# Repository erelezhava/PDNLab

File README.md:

# PDNLab DC

Open-source DC power-integrity (IR drop) solver for PCBs. Own solver code, KiCad 10 boards as the first input, Apache-2.0.

**Status: Phase 2 (real boards), no release yet.** A KiCad 10 board runs end to
end: `init`, `check` and `run` (below) give a settled DC drop with maps and tables.

Current support and limits:

- Input: KiCad 10 boards, through KiCad's IPC-2581 export (`kicad-cli`, run for
  you by `init`, `check` and `run`). Other EDA tools are not supported.
- One rail per setup file: one `[[source]]` and its `[[load]]`s. Several rails
  sharing GND are refused for now: GND solved per rail would leave out the other
  rails' return current (planned; see the [roadmap](docs/roadmap.md), increment G).
- A board run needs the external Gmsh executable on `PATH` (see Setup).
- Not checked yet: copper outside the board outline (KiCad's DRC catches it; the
  importer does not read the outline), and copper of two nets that only touch
  along an edge (an overlap is caught). Run KiCad's DRC first.
- Results are for review, not sign-off: release 0.1 waits for its gates (see
  the [roadmap](docs/roadmap.md)).

Measured results and limitations are in [the result log](docs/DECISIONS.md); the
current licences and packaging boundaries in the
[dependency inventory](docs/dependency-license-audit.md).

See the [development plan](docs/project-plan.md) for scope, architecture,
experiments and release gates.

## Setup

```sh
uv sync          # creates .venv with numpy, scipy, meshio and pytest
uv run pytest    # runs the analytic tests
```

Without uv: `pip install -e . pytest`, then `pytest`.

Experiments 2 to 4 also need the external Gmsh executable on `PATH`. On Ubuntu:

```sh
sudo apt install gmsh
gmsh --version
```

Without Gmsh, the integration tests that need it are skipped. CI installs it so
those tests run there too. The solver never imports the Gmsh Python API.

## Describing a simulation

A simulation is described by a TOML setup file, by pins. Start from the KiCad
board: `init` exports it with KiCad's own `kicad-cli` (on `PATH`, or named by
`PDNLAB_KICAD_CLI`) into a `pdnlab/` folder in the project and writes a form to
fill in there. An IPC-2581 export (`.xml`) works too.

```sh
uv run pdnlab-dc init path/to/project/board.kicad_pcb
# writes path/to/project/pdnlab/board.xml and path/to/project/pdnlab/setup.toml
# fill in plating_um, the [[source]] and the [[load]]s; pin names are listed at
# the bottom of the file, net by net
uv run pdnlab-dc check path/to/project/pdnlab/setup.toml   # says what will be simulated
```

A `[[source]]` holds its `power_pins` at `volts`, a `[[load]]` draws `amps`; each
lists its `power_pins` and `gnd_pins`, and the pins of one list are joined (one
group). `U1.*` means every pin of U1 on that list's net, so hidden power and GND
pins are not missed; `check` says how many pins each wildcard added. When the
`.kicad_pcb` is newer than its export, `check` and `run` export it again.

## Running a simulation

```sh
uv run pdnlab-dc run path/to/project/pdnlab/setup.toml
```

The rail's power net and the GND net are solved as separate networks carrying
the same currents; each load sees V(power) − V(GND). One rail per setup file for
now (see the limits above). The mesh is made finer
(scale 1, 0.5, 0.25, 0.125) until the voltage every load sees changes by at most
the tolerance (default 10 µV + 1 % of its drop; `[options] tolerance_uv` and
`tolerance_percent`).

Results go to `results/<setup name>/` next to the setup file (in a KiCad
project: `pdnlab/results/setup/`); earlier results are replaced only with
`--force`:

- `summary.txt`: per load the voltage it sees and its drop, split into power and
  GND; the refinement check round by round, with memory per round; per net
  losses, the solver's checks, current-density hot spots per layer (peak, and
  averaged over a 0.25 mm disk) and the highest barrel currents; the
  assumptions.
- `loads.csv`, `pins.csv` (each pin's share of its group's current), `vias.csv`
  (each plated hole's largest barrel current).
- Per net and layer: `<net>_<layer>.vtu` for ParaView (voltage, drop in mV,
  current density in A/mm²) and `<net>_<layer>_voltage.png` /
  `<net>_<layer>_current.png`.

Memory: a refinement round is not started if its predicted memory (from the last
round's measured peak, with a 1.5× margin) exceeds `[options] max_memory_gb`
(default: half of the computer's RAM) or the free memory. The last completed
round is then reported, marked NOT SETTLED, and `run` exits with code 2. A hard
ceiling (the limit + 2 GB, inherited by Gmsh) turns a wrong estimate into an
out-of-memory message instead of a frozen machine. Exit codes: 0 settled, 1 not
solved (the message says what to fix), 2 not settled.

## Prepared solver (phase 1)

Existing assembly, ties and resistor primitives remain in `pdnlab_dc.fem`;
barrel resistance is in `pdnlab_dc.vias`. Prepare the final electrical matrix
after tying nodes and stamping resistors:

```python
from pdnlab_dc.solver import prepare_fixed_voltages

system = prepare_fixed_voltages(matrix, fixed_nodes)
v = system.solve(3.3, injected_current)  # positive into copper; sinks negative
v_next = system.solve(3.3, next_current)  # reuses the same factorization
# Optional: observed voltage per +1 A, with fixed voltages at zero:
z = system.transfer_resistance(load_nodes, batch_size=8)
print(system.stats, system.last_solve)
```

Preparation copies the matrix and fixed indices. Reprepare if conductances or
fixed-node membership change; current and fixed-voltage values may change
without preparation. The one-shot `fem.solve_fixed_voltages` remains compatible
and delegates to this solver. Every component still needs a fixed node.
Sources here are voltages to a reference, not arbitrary two-terminal sources.
The input is a conservative nodal matrix, with ground represented explicitly;
material nonzero row sums (including implicit ground shunts) are rejected.
Each connected network is solved relative to one of its fixed voltages, then
shifted back, reducing sensitivity to the rail's absolute voltage.

Transfer extraction bounds full-field RHS/solution columns by `batch_size`,
but its returned dense observation-by-injection matrix can still be large.
It is never built by `solve`. A selected electrical node may represent a tied
finite contact; selecting a bare mesh vertex does not validate point-contact
physics. Explicit area contacts are available through the network interface below.

`system.stats` reports preparation/factorization time, nonzero counts and
sparse-array bytes; it does not measure peak RSS or native LU workspace.
`system.last_solve` records elapsed time and RHS batching. Independent loss
integration and conservation checks remain in `pdnlab_dc.checks` and require
original sheet geometry and branch data from the caller.
Checks normalize reactions and terminal power to the same per-network origin.
They require both global and per-network current balance; independent loss
integration and per-via checks retain their existing tolerances.

Run the synthetic performance probe (no private boards):

```sh
uv run python experiments/phase1_solver_benchmark.py
```

The primary probe solves relative to zero. A separate 3.3 V probe now gates
reference invariance and conservation. The formerly failing power-check case
and its correction are recorded in the result log. Very large common-mode
voltages relative to the drop remain limited by floating-point resolution.
The real-board experiment's transfer/scenario workflow has not been migrated.

## Named synthetic networks

`pdnlab_dc.network.Network` composes the validated primitives without manual
sparse-matrix wiring. All geometry/material inputs use SI units:

```python
from pdnlab_dc.network import Network
from pdnlab_dc.simple_meshes import rectangle_mesh

nodes, triangles, left, right = rectangle_mesh(0.05, 0.005, 12, 4)
net = Network()
net.add_sheet("top", nodes, triangles, sheet_conductance=35e-6 / 1.724e-8)
net.add_terminal("source", "top", left)
net.add_terminal("load", "top", right)
prepared = net.prepare(["source"])
result = prepared.solve({"source": 3.3}, {"load": 0.1})
assert result.passed, result.checks
next_case = prepared.solve({"source": 3.3}, {"load": 0.2})  # same LU
```

Terminal selections are disjoint node groups on one sheet. By default their
nodes are tied equipotential, representing an ideal soldered pad/rim. Passing
explicit `weights=[...]` leaves them untied and allocates sink current by those
nonnegative fractions, in selected-node order. There is no implicit equal
allocation for an untied group. Use `add_contact` below for explicit finite-area
polygons; a bare vertex still has point-contact mesh dependence.

Use `add_resistor(name, a, b, resistance)` between equipotential terminals.
Use `add_barrel(name, a, b, length=..., inner_radius=..., outer_radius=...,
resistivity=...)` between terminals declared with `rim=True` on distinct
sheets. Rims stay separate electrical unknowns; each declared rim must have
an incident branch. The caller supplies contacted layers and copper radii.

Preparation snapshots the builder. Source membership then stays fixed;
`solve` requires exactly those source-voltage names and accepts nonnegative
sink currents by load-terminal name. Unspecified loads draw zero. Unknown
loads, loads at fixed sources, overlapping selections and floating components
raise errors instead of silently changing a case. Source terminal currents
may be positive (supplying) or negative (absorbing).

Results include electrical and per-sheet voltages, per-selected-node terminal
voltages, external terminal currents (positive into copper), branch currents
(declared a → b), independently integrated sheet/branch losses, timings and
conservation checks. Rim KCL includes sheet, every incident branch and any
external current at that rim. Check `result.passed`: failed checks are returned
with their residuals and tolerances. `prepared.node_map` gives copies mapping
original sheet nodes to electrical unknowns.

`prepared.stats` separates sheet assembly, area-contact selection, composition
and solver preparation;
`prepared.last_solve` exposes the last low-level solve/transfer timing and RHS
statistics. Its solver sparse-byte count excludes the wrapper's check matrix,
original sheet matrices, geometry and mappings; it is not whole-model memory.
`prepared.transfer_resistance(["load"], batch_size=8)` optionally extracts Z
in requested name order for equipotential terminals only.

Run the three-layer analytic example with named pads/rims and two barrel
segments, at two mesh resolutions and two current levels:

```sh
uv run python experiments/phase1_network_cases.py
```

## Finite-area contacts

`Network.add_contact(name, sheet, region, model=...)` selects an explicit
Shapely `Polygon` in mesh coordinates (metres), including its position and area:

```python
from shapely.geometry import box

# For the strip above: feed ends on the first grid line; touch may cut cells.
contact_net = Network()
contact_net.add_sheet("top", nodes, triangles, 35e-6 / 1.724e-8)
contact_net.add_contact("feed", "top", box(0, 0, 0.05 / 12, 0.005))
contact_net.add_contact("touch", "top", box(0.025, 0, 0.035, 0.005),
                        model="uniform_current")
contact_model = contact_net.prepare(["feed"])
case = contact_model.solve({"feed": 3.3}, {"touch": 0.1})
assert case.passed, case.checks
print(case.contact_voltages_v["touch"])  # area-average copper voltage
```

- `equipotential` (default) is an ideal electrode shorting only its specified
  area. Its boundary must conform to the existing mesh: materially cut
  triangles raise instead of silently changing the electrode's size. It can
  be a fixed-voltage source or a current sink; the solve determines sharing.
- `uniform_current` prescribes constant current per area without tying the
  copper. Triangle intersections are integrated to obtain FEM nodal load
  weights and the area-average voltage. It supports current sinks, including
  patches whose edges cut triangles. Its support vertices may lie outside the
  polygon; the integrated patch itself is not enlarged. It is not a fixed-
  voltage source or an equipotential terminal for transfer extraction.

These are distinct idealizations of contact behaviour. No contact resistivity,
pressure-dependent distribution or 3D interface model is inferred. The region
must be a valid positive-area 2D polygon fully covered by nonoverlapping copper
elements. Clipping outside copper, nearest-node fallback and zero-area point
regions are rejected. Shared terminal support is still unsupported: refine if
two disjoint physical contacts share coarse-mesh vertices. Automatic remeshing
and pad/importer integration remain later work.

`prepared.contact_info` reports model, bounds, requested/covered area and support
size. `result.contact_voltages_v` reports the electrode voltage or uniform-area
mean; `terminal_voltages_v` still returns all selected nodal voltages. The
standalone `pdnlab_dc.contacts.select_area_contact` exposes the selection and
weights for other callers. Geometry checks use a 1e-10 relative area tolerance;
electrical conservation and analytic tolerances are unchanged.

Run finite-electrode and uniform-patch convergence against analytic references,
with a separate mathematical-point diagnostic:

```sh
uv run python experiments/phase1_contact_cases.py
```

The diagnostic point's voltage grows with refinement; it is not reported as a
physical contact-resistance prediction. The finite circular electrode uses a
fixed 128-sided polygon, so its circle-reference error includes polygon geometry.

## Phase 2 board-model scaffold

`pdnlab_dc.board` contains immutable neutral records for source provenance,
layers, nets, copper features, physical pin pads and drill features. `BoardModel`
validates IDs, references, SI dimensions, polygon topology and layer/drill
ordering. It does not parse XML, transform/repair geometry or infer electrical
contacts. See the [development contract](docs/phase2-board-model-contract.md)
and `tests/test_board.py` for synthetic examples.

`pdnlab_dc.ipc2581_metadata.read_ipc2581_metadata(path)` reads only the header
and stackup of an IPC-2581 revision C file in millimetres: the input hash,
exporter version when declared, and ordered copper layers with centre Z and
thickness in metres. It returns `Ipc2581Metadata`, not a board: no nets,
tracks, pads, zones or drills are read, and unsupported revisions, units or
stackups raise. It has been tested on synthetic XML only.

`pdnlab_dc.ipc2581_copper.read_ipc2581_copper(path)` adds nets, filled-zone
contours and tracks. It returns `Ipc2581Copper`, again not a board: `Net` records
from the export's `Set` net names; one `CopperFeature` of kind `fill` per zone
contour in metres with its holes; one of kind `track` per straight or arc track,
outlined with round ends at a 1 µm chord error (`pdnlab_dc.track_outline`);
one of kind `pad` per component pad and `via` per via on every copper layer, as
solid outlines from the export's shape dictionary (`pdnlab_dc.pad_outline`); one
`DrillFeature` per drill hole, linked to its pad and via copper by `drill_id`
but not cut out of it (the finished-hole size is a setup value); and the
non-copper layers it did not inspect. Any other
copper (teardrops, copper text and graphics, footprint-owned zones) raises, so
copper on a net is never silently left out. KiCad's fractured fills are split
back into outline and holes at their zero-width slits; any other unsupported or
invalid geometry raises. Tracks are checked against KiCad's own board file on the
public board in `tests/fixtures/arc_track`; pads and vias against KiCad's own SVG
plot of the public board in `tests/fixtures/pad_shapes`; fills meeting pads
(thermal spokes, solid connections, clearances) against KiCad's plot of the
public board in `tests/fixtures/thermal_relief`.

`pdnlab_dc.ipc2581_board.read_ipc2581_board(path)` assembles all of this into
one `BoardModel`, adding a `PinPad` per physical component pad (its copper on each
layer and its hole). Copper is not yet merged per net and layer, holes are not
cut and nothing is meshed or solved from it. Every pin of the public boards is
checked against KiCad's own board file.

`pdnlab_dc.copper_cleanup.clean_copper(board, plating_m)` merges each net's
copper per layer into separate pieces and cuts the holes (plated holes at the
finished radius plus the plating thickness, which is required). Shorts between
nets, annular-ring breakouts and slivers raise. The pieces match KiCad's plot of
the public boards piece for piece.

`pdnlab_dc.board_mesh.mesh_net(clean, board, net_id)` meshes one net's pieces
with Gmsh (an external program), with default size rules and one scale factor
that a refinement check halves. On every case measured, the first mesh is
within 1% of the converged resistance.

`pdnlab_dc.board_network.build_net_network(board, clean, mesh, pins)` turns one
net into a solvable network: a sheet per layer, via and pin barrels between the
layers, and an equipotential contact on each chosen pin's pad. If any piece of the
net is not joined to the rest (an island), it stops and nothing is simulated.

## Phase 0 experiments

| # | Experiment | Status |
| --- | --- | --- |
| 1 | Plain rectangle on a hand-made mesh against R = ρL/(Wt) | Passes, see `tests/test_exp01_rectangle.py` |
| 2 | Rectangle through external Gmsh, MSH 4.1 and named boundary tags | Passes, see `tests/test_exp02_gmsh_rectangle.py` |
| 3 | Annular ring with a tied inner rim and mesh refinement | Passes, see `tests/test_exp03_annular_ring.py` |
| 4 | Two layer rings connected by a finite via barrel resistor | Passes, see `tests/test_exp04_two_rings.py` |
| 5 | Current conservation, per-layer via KCL and independent power balance across experiments 1–4 | Passes, see `tests/test_exp05_balances.py` |
| 6 | KiCad 10 IPC-2581 export against saved native board data | Export coverage audits and a real-net reader/solve comparison recorded; IPC-2581 confirmed by the maintainer. One board/net is not general importer validation. |
| 7 | padne real-net reference comparison | Reference run recorded; raw drop discrepancy traced to terminal modelling. KiPI dropped by the maintainer. See [results](docs/DECISIONS.md). |
| 8 | Real net through geometry cleanup, Gmsh and DC solve | Completed experimentally, including multilayer vias and mesh-convergence checks; direct and IPC-2581 readers compared. See [results](docs/DECISIONS.md). |

An extra regression test, `tests/test_offcentre_via.py`, checks a via placed
off-centre in a circular sheet, where current crowds onto one side of the rim.
Its closed-form reference is derived in
[docs/off-centre-via-reference.md](docs/off-centre-via-reference.md).

Print the numbers with `uv run python experiments/exp01_rectangle.py`.

Run the Gmsh round trip with:

```sh
uv run python experiments/exp02_gmsh_rectangle.py
# Keep .geo files, .msh files and results.json for inspection:
uv run python experiments/exp02_gmsh_rectangle.py --output-dir /tmp/pdnlab-exp02
```

Results and recommendations are recorded in [docs/DECISIONS.md](docs/DECISIONS.md).

Run the ring experiment with:

```sh
uv run python experiments/exp03_annular_ring.py
# Keep both mesh levels and their measured results:
uv run python experiments/exp03_annular_ring.py --output-dir /tmp/pdnlab-exp03
```

Run the two-layer via experiment with:

```sh
uv run python experiments/exp04_two_rings.py
# Keep each layer's geometry, mesh and combined results:
uv run python experiments/exp04_two_rings.py --output-dir /tmp/pdnlab-exp04
```

Run all four experiments with the conservation gates:

```sh
uv run python experiments/exp05_balances.py
# Keep the individual results and a combined summary:
uv run python experiments/exp05_balances.py --output-dir /tmp/pdnlab-exp05
```

Each experiment now includes current and power checks in its pass/fail result.
JSON outputs include residuals, tolerances and individual via-rim results where
applicable. Sheet heat is integrated from triangle voltage gradients; resistor
heat is computed from branch voltage drops.

Run the export inspection with KiCad 10 installed:

```sh
# Uses the installed KiCad StickHub demo without modifying it:
uv run python experiments/exp06_kicad_export.py --output-dir /tmp/pdnlab-exp06
# Or audit your own saved board:
uv run python experiments/exp06_kicad_export.py --board /path/to/board.kicad_pcb --output-dir /tmp/pdnlab-exp06-custom
```

The export audit compares saved fills, stackup, pin/net mappings and via holes.
An additional geometry audit checks tracks, pad copper and pad holes; use
`--strict` to make it gate the exit code. Unsupported geometry fails that
audit. The experimental IPC-2581 reader also compares one net's geometry and
solved drops against the direct board reader. This is not a production importer
or validation of Altium/OrCAD X exports. Refill and save your board first; the
audit cannot establish whether cached fills are current. Plating thickness
remains an explicit setup input.

The KiCad integration test is optional and skips without KiCad 10 and the
installed StickHub demo. CI currently installs Gmsh, but does not install KiCad;
the XML inspection unit tests still run there.

Experiment 7 recorded a padne comparison on the private real-board net. The
raw drops disagree because the terminal models differ; downstream comparisons
and remaining limitations are recorded in [DECISIONS.md](docs/DECISIONS.md).
KiPI was dropped from the current plan. The original StickHub reference run
was not performed. Historical setup instructions remain in
[experiment 7 setup](docs/experiment-07-setup.md).

## Layout

| Path | Content |
| --- | --- |
| `docs/project-plan.md` | Development plan, milestones and validation criteria |
| `docs/DECISIONS.md` | Experiment results and recommendations |
| `docs/off-centre-via-reference.md` | Derivation of the off-centre via reference |
| `docs/experiment-07-setup.md` | Reference comparison setup and historical installation instructions |
| `src/pdnlab_dc/` | Solver package |
| `tests/` | Analytic tests, run on every commit |
| `experiments/` | Phase 0 experiment scripts, one per experiment |

## Licence

Apache-2.0, see [LICENSE](LICENSE). Gmsh and KiCad are used only as external programs and are not part of this repository.

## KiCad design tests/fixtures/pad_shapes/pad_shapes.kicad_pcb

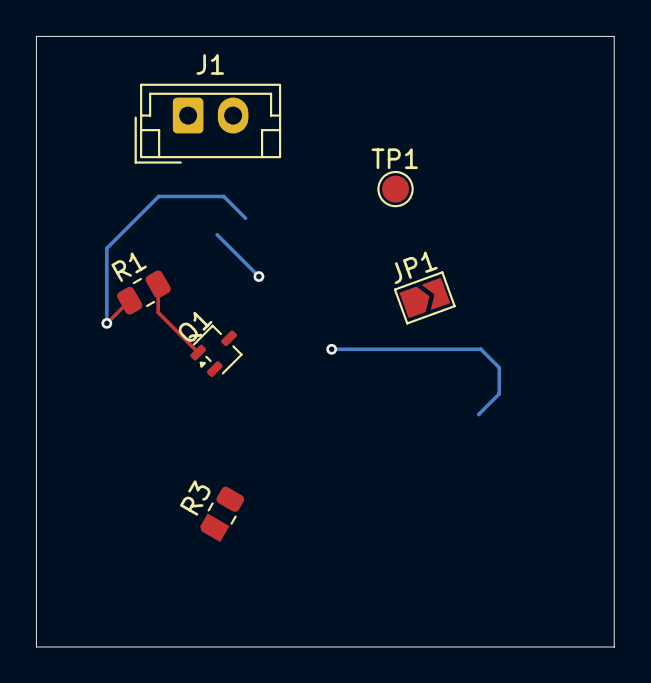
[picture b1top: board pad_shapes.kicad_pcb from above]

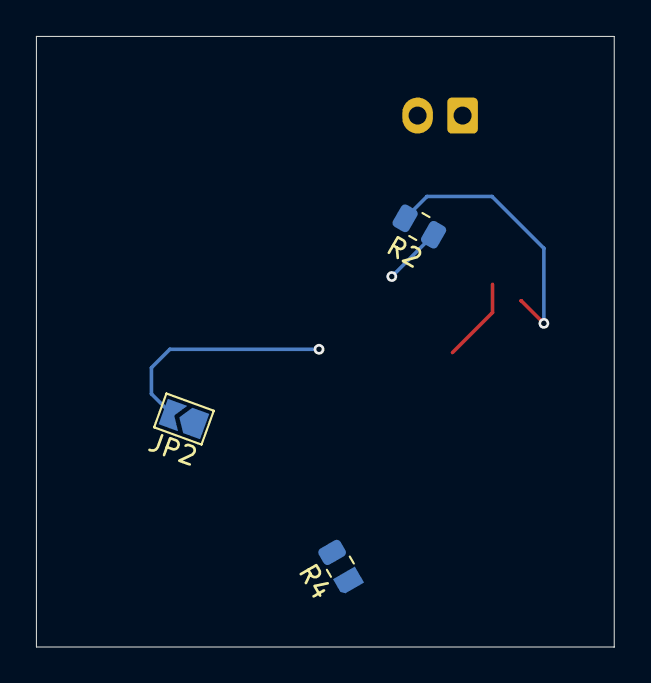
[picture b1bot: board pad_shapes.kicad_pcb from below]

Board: 4 copper layers, 32.1 x 33.9 mm, 9 parts (3 on the bottom side), 3 nets.

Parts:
J1: Conn_01x02_Pin; JST_EH_B2B-EH-A_1x02_P2.50mm_Vertical
JP1, JP2: SolderJumper_2_Open; SolderJumper-2_P1.3mm_Open_TrianglePad1.0x1.5mm
Q1: 2SC4213; SOT-323_SC-70
R1, R2, R3, R4: R; R_0805_2012Metric
TP1: TestPoint; TestPoint_Pad_D1.5mm

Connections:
unnamed: JP2.2 (B_2), R2.1
unnamed: Q1.1 (B_1), R1.2
unnamed: R1.1, R2.2
